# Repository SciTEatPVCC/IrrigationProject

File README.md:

IrrigationProject
=================

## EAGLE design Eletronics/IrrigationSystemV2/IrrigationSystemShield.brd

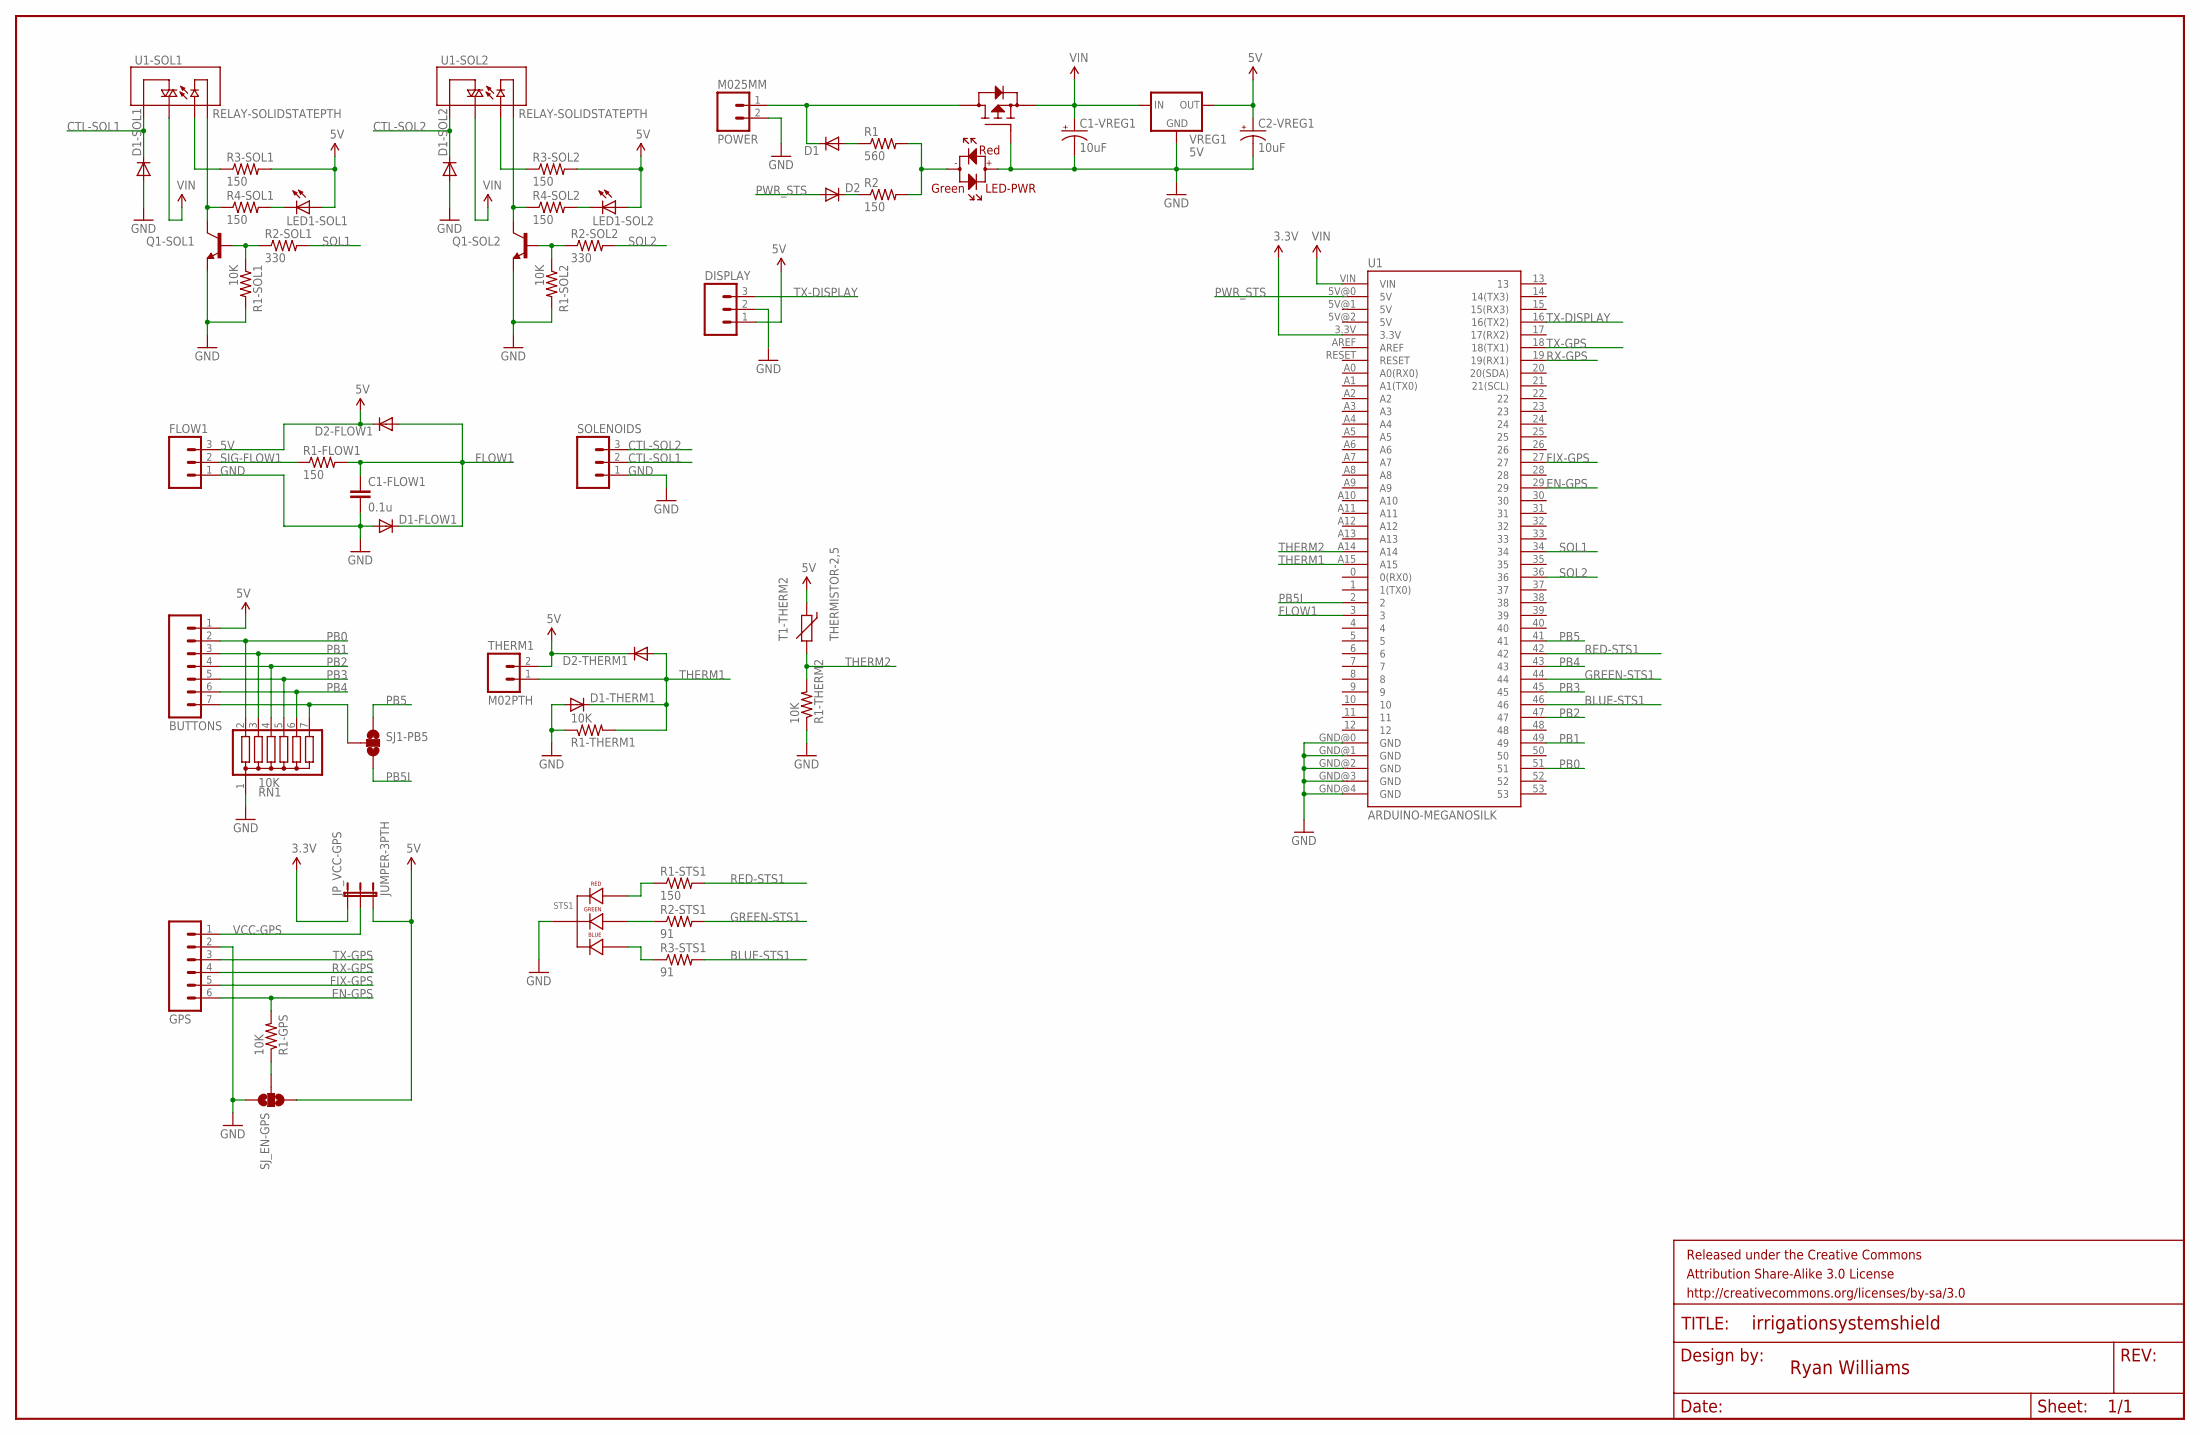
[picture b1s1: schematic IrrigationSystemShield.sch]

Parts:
BUTTONS: M07; 1X07
C1-FLOW1: 0.1u; CAP-PTH-5MM
C1-VREG1, C2-VREG1: 10uF; CPOL-RADIAL-10UF-25V
D1, D1-SOL1, D1-SOL2, D2: DIODEPTH; DIODE-1N4001
D1-FLOW1, D1-THERM1, D2-FLOW1, D2-THERM1: DIODE1N4148; DIODE-1N4148
DISPLAY: M03JST-PTH; JST-3-PTH
FET-1: P-FET; FQP27P06
FLOW1: M03-SCREW-5MM; SCREWTERMINAL-5MM-3
FRAME1: FRAME-LEDGER; CREATIVE_COMMONS
GPS: M06SIP; 1X06
JP_VCC-GPS: JUMPER-3PTH; 1X03
LED1-SOL1, LED1-SOL2: LED5MM
LED-PWR: LED-BIPOLARHGL*3362; LED-5MM
POWER: M025MM; SCREWTERMINAL-5MM-2
Q1-SOL1, Q1-SOL2: TRANSISTOR_NPNTO92; TO-92
R1: 560; AXIAL-0.5
R1-FLOW1, R1-STS1, R2, R3-SOL1, R3-SOL2, R4-SOL1, R4-SOL2: 150; AXIAL-0.4
R1-GPS, R1-SOL1, R1-SOL2, R1-THERM1, R1-THERM2: 10K; AXIAL-0.4
R2-SOL1, R2-SOL2: 330; AXIAL-0.4
R2-STS1, R3-STS1: 91; AXIAL-0.4
RN1: 10K; SIL7
SJ1-PB5: SOLDERJUMPER_2WAYS; SJ_3
SJ_EN-GPS: SOLDERJUMPER_2WAYS; SJ_3
SOLENOIDS: M03-SCREW-5MM; SCREWTERMINAL-5MM-3
STS1: LED-RGB-CC-THRUDIFFUSE; LED-RGB-THRU
T1-THERM2: THERMISTOR-2,5; RS-2,5
THERM1: M02PTH; 1X02
U1: ARDUINO-MEGANOSILK; ARDUINO_MEGA_NOSILK
U1-SOL1, U1-SOL2: RELAY-SOLIDSTATEPTH; RELAY-S108T02
VREG1: 5V; TO220-IGO

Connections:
3.3V: JP_VCC-GPS.1, U1.3.3V
5V: BUTTONS.1, C2-VREG1.1 (+), D2-FLOW1.C, D2-THERM1.C, DISPLAY.1, FLOW1.3, JP_VCC-GPS.3, LED1-SOL1.A, LED1-SOL2.A, R3-SOL1.P$2 (2), R3-SOL2.P$2 (2), SJ_EN-GPS.3, T1-THERM2.1, THERM1.2, VREG1.OUT
BLUE-STS1: R3-STS1.P$2 (2), U1.46
CTL-SOL1: D1-SOL1.C, SOLENOIDS.2, U1-SOL1.1 (T1)
CTL-SOL2: D1-SOL2.C, SOLENOIDS.3, U1-SOL2.1 (T1)
EN-GPS: GPS.6, R1-GPS.P$2 (2), U1.29
FIX-GPS: GPS.5, U1.27
FLOW1: C1-FLOW1.1, D1-FLOW1.C, D2-FLOW1.A, R1-FLOW1.P$2 (2), U1.3
GND: C1-FLOW1.2, C1-VREG1.2 (-), C2-VREG1.2 (-), D1-FLOW1.A, D1-SOL1.A, D1-SOL2.A, D1-THERM1.A, DISPLAY.2, FET-1.GATE, FLOW1.1, GPS.2, LED-PWR.ANODE, POWER.2, Q1-SOL1.1 (E), Q1-SOL2.1 (E), R1-SOL1.P$2 (2), R1-SOL2.P$2 (2), R1-THERM1.P$1 (1), R1-THERM2.P$1 (1), RN1.1, SJ_EN-GPS.1, SOLENOIDS.1, STS1.2 (CATHODE), U1.GND@0 (GND), U1.GND@1 (GND), U1.GND@2 (GND), U1.GND@3 (GND), U1.GND@4 (GND), VREG1.GND
GREEN-STS1: R2-STS1.P$2 (2), U1.44
unnamed: Q1-SOL2.2 (B), R1-SOL2.P$1 (1), R2-SOL2.P$1 (1)
unnamed: Q1-SOL1.2 (B), R1-SOL1.P$1 (1), R2-SOL1.P$1 (1)
unnamed: LED1-SOL1.K (C), R4-SOL1.P$2 (2)
unnamed: Q1-SOL1.3 (C), R4-SOL1.P$1 (1), U1-SOL1.4 (-)
unnamed: R3-SOL1.P$1 (1), U1-SOL1.3 (+)
unnamed: LED1-SOL2.K (C), R4-SOL2.P$2 (2)
unnamed: Q1-SOL2.3 (C), R4-SOL2.P$1 (1), U1-SOL2.4 (-)
unnamed: R3-SOL2.P$1 (1), U1-SOL2.3 (+)
unnamed: D1.C, FET-1.DRAIN, POWER.1
unnamed: R1-STS1.P$1 (1), STS1.1 (RED_CATHODE)
unnamed: R1-GPS.P$1 (1), SJ_EN-GPS.2
unnamed: R2-STS1.P$1 (1), STS1.3 (GREEN_CATHODE)
unnamed: R3-STS1.P$1 (1), STS1.4 (BLUE_CATHODE)
unnamed: D2.C, R2.P$1 (1)
unnamed: LED-PWR.CATHODE, R1.P$2 (2), R2.P$2 (2)
unnamed: D1.A, R1.P$1 (1)
PB0: BUTTONS.2, RN1.2, U1.51
PB1: BUTTONS.3, RN1.3, U1.49
PB2: BUTTONS.4, RN1.4, U1.47
PB3: BUTTONS.5, RN1.5, U1.45
PB4: BUTTONS.6, RN1.6, U1.43
PB5: SJ1-PB5.1, U1.41
PB5I: SJ1-PB5.3, U1.2
PB5RAW: BUTTONS.7, RN1.7, SJ1-PB5.2
PWR_STS: D2.A, U1.5V@0 (5V)
RED-STS1: R1-STS1.P$2 (2), U1.42
RX-GPS: GPS.4, U1.19 (19(RX1))
SIG-FLOW1: FLOW1.2, R1-FLOW1.P$1 (1)
SOL1: R2-SOL1.P$2 (2), U1.34
SOL2: R2-SOL2.P$2 (2), U1.36
THERM1: D1-THERM1.C, D2-THERM1.A, R1-THERM1.P$2 (2), THERM1.1, U1.A15
THERM2: R1-THERM2.P$2 (2), T1-THERM2.2, U1.A14
TX-DISPLAY: DISPLAY.3, U1.16 (16(TX2))
TX-GPS: GPS.3, U1.18 (18(TX1))
VCC-GPS: GPS.1, JP_VCC-GPS.2
VIN: C1-VREG1.1 (+), FET-1.SOURCE, U1.VIN, U1-SOL1.2 (T2), U1-SOL2.2 (T2), VREG1.IN

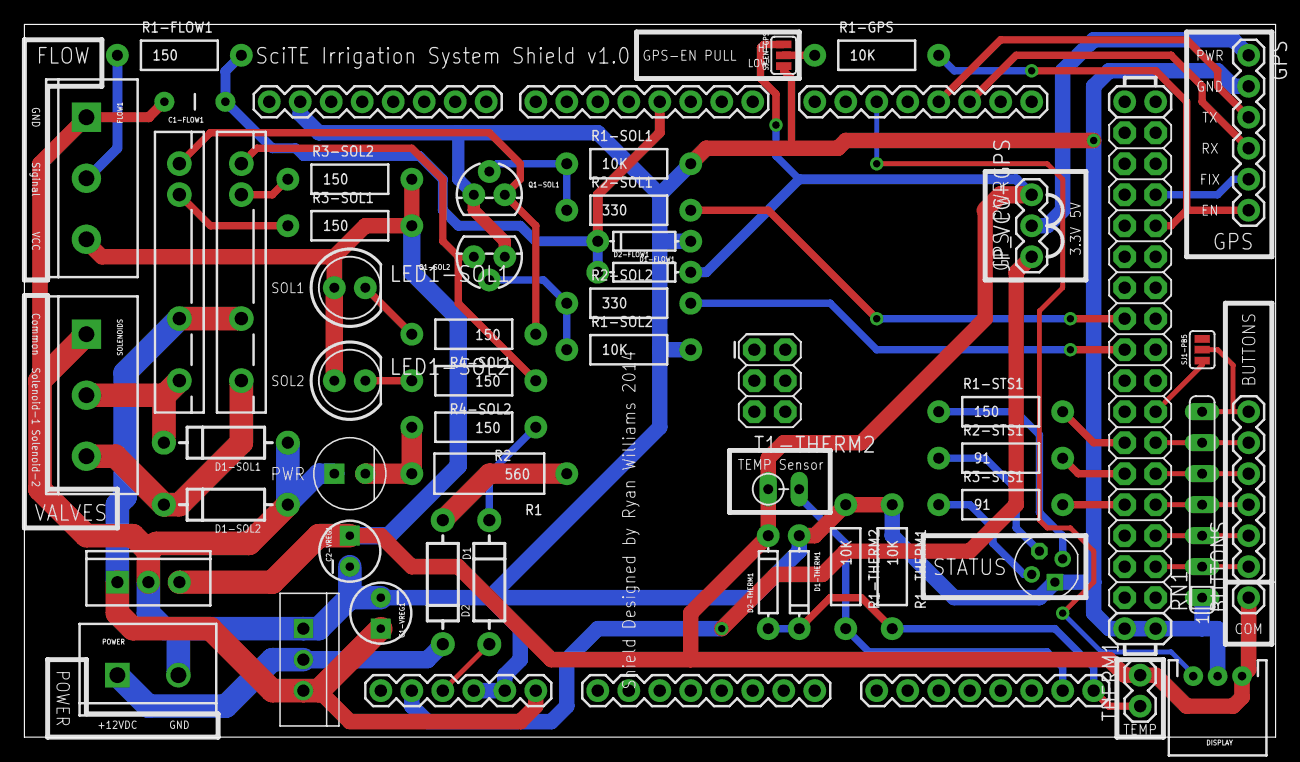
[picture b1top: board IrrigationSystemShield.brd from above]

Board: 2 copper layers, 102.5 x 58.4 mm, 52 parts (0 on the bottom side), 46 nets.

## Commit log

2014-03-28 Added ".DS_store" to .gitignore
    .DS_store is used by Mac OS X finder to store metadata about the
    folder. This might cause file system problems if this file is cloned on
    another system
2014-03-28 Added Eagle Files for the shield to this repo.
2014-04-03 Changed the Library
2014-04-03 Closed Project
2014-04-14 Added ability to add Interrupt to PB5.
    Updated Schematic to include interrupt. Need to run trace for
    interrupt. If trace is not run PB5 will still work as a non interrupted
    pin.

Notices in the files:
parts and their libraries:
SparkFun-Aesthetics: Licensing: CC v3.0 Share-Alike You are welcome to use this library for commercial purposes.
SparkFun-Aesthetics: Released under the Creative Commons Attribution Share-Alike 3.0 License
SparkFun-Aesthetics: http://creativecommons.org/licenses/by-sa/3.0
